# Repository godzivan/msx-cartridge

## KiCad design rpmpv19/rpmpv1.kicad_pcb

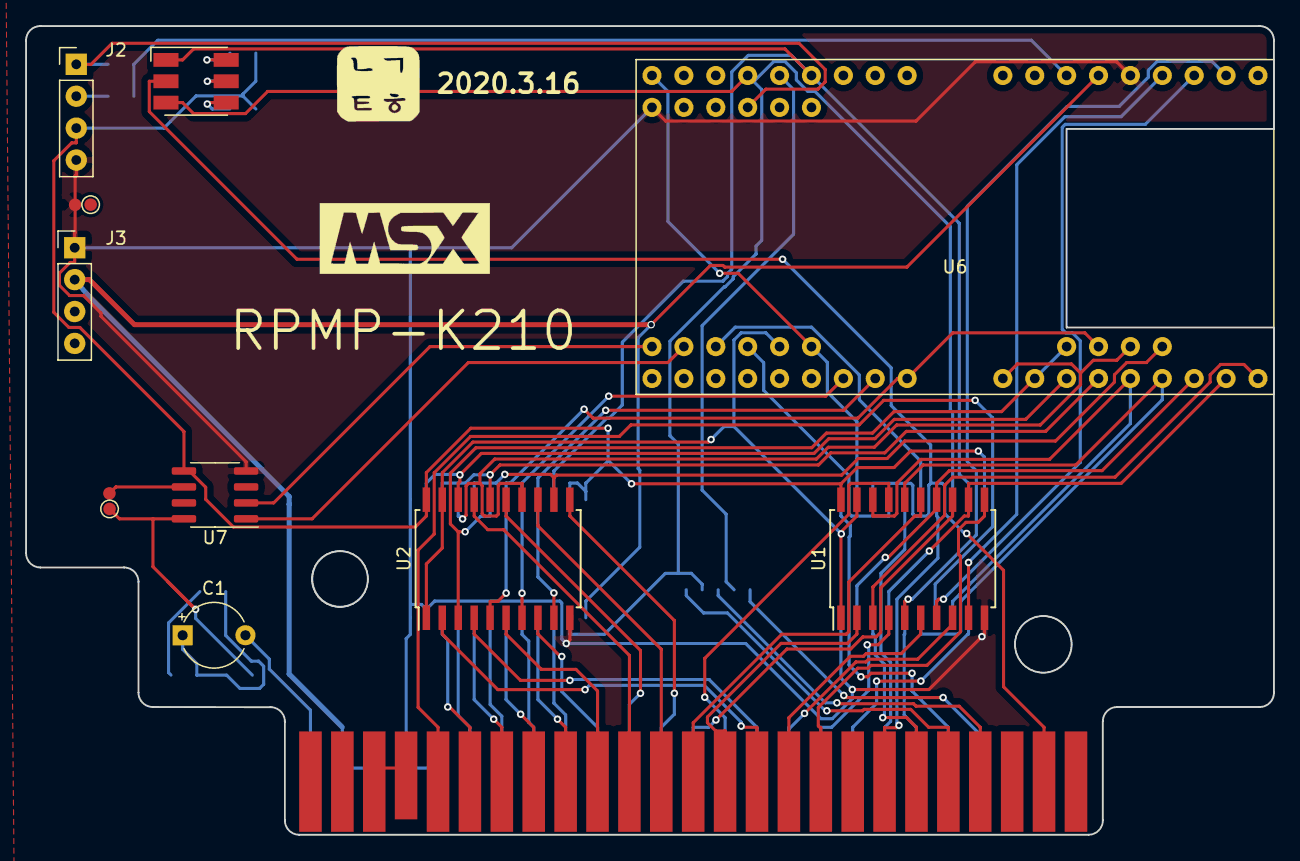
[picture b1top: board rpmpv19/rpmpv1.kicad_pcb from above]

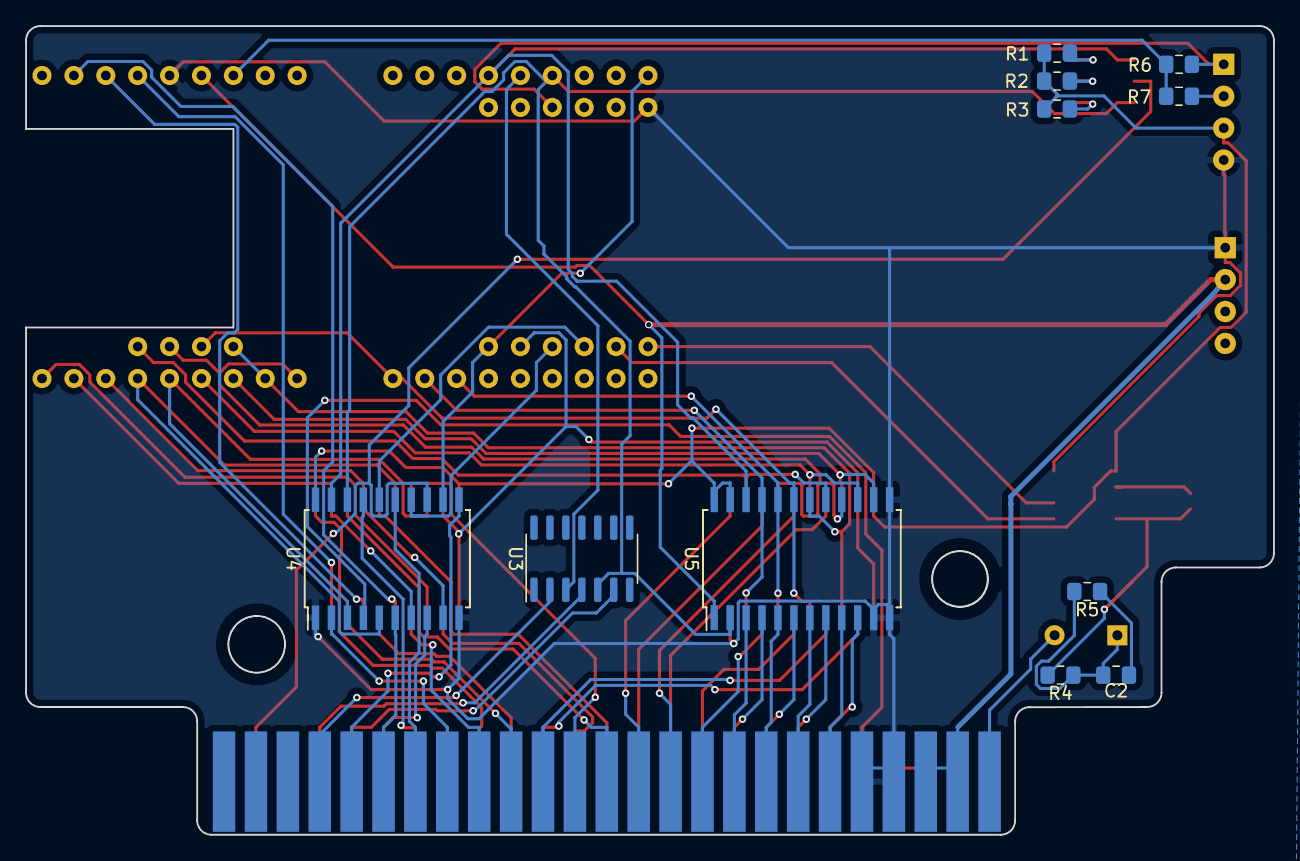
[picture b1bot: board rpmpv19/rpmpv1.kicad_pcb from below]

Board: 2 copper layers, 99.4 x 64.4 mm, 24 parts (11 on the bottom side), 75 nets.

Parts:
C1: CP; CP_Radial_Tantal_D5.0mm_P5.00mm
C2: C; C_0805_2012Metric_Pad1.15x1.40mm_HandSolder
D1: LED_RGB; LED_RGB_5050-6
G1: LOGO; srxg10
G2: LOGO
J2: Conn_01x04; PinHeader_1x04_P2.54mm_Vertical
J3: Conn_01x04_Male; PinHeader_1x04_P2.54mm_Vertical
P1: CONN_02X25; card_edge_connector
R1, R2, R3, R4, R5, R6, R7: R; R_0805_2012Metric_Pad1.15x1.40mm_HandSolder
U1, U2, U4: 74HC244; SOIC-20W_7.5x12.8mm_Pitch1.27mm
U3: 74LS07; SOIC-14_3.9x8.7mm_P1.27mm
U5: LVC4245; SOIC-24W_7.5x15.4mm_Pitch1.27mm
U6: SipeedMaixBit; maix_bit
U7: PT8211; SOIC-8_3.9x4.9mm_P1.27mm
W1, W2: TEST; TestPoint_Pad_D1.0mm

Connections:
/3V3: R6.1, R7.1, U6.49
/5V0: J3.2, P1.45, P1.47, U5.1, U6.48
/A0: P1.28, U2.13
/A1: P1.27, U2.11
/A2: P1.30, U2.17
/A3: P1.29, U2.15
/A4: P1.32, U2.6
/A5: P1.31, U2.8
/A6: P1.22, U2.2
/A7: P1.21, U2.4
/A8: P1.24, U1.2
/A9: P1.17, U1.4
/A10: P1.20, U1.6
/A11: P1.19, U1.8
/A12: P1.23, U1.17
/A13: P1.26, U1.15
/A14: P1.25, U1.13
/A15: P1.18, U1.11
/ADDR: U1.1, U1.19, U2.1, U2.19, U6.37
/BUSDIR: P1.10, U3.6
/CLK: P1.42, U4.4
/D0: P1.34, U5.4
/D1: P1.33, U5.3
/D2: P1.36, U5.6
/D3: P1.35, U5.5
/D4: P1.38, U5.8
/D5: P1.37, U5.7
/D6: P1.40, U5.10
/D7: P1.39, U5.9
/DAT_DIR: D1.3, U3.5, U4.18, U5.2, U6.32
/DAT_EN: D1.1, U4.19, U5.22, U6.30
/GND: J2.4, J3.1, P1.41, P1.43, U1.10, U2.10, U4.1, U4.10, U5.11, U5.12, U5.13, U6.47, U7.4, W2.2
/INT: P1.8, U3.4
/IORQ: P1.11, U4.6
/M1: P1.9, U4.11
/MREQ: P1.12, U4.8
/PCM_RCK: U6.40, U7.1
/PCM_WS: U6.41, U7.2
/RA8: U1.18, U4.3, U6.17
/RA9: U1.16, U4.5, U6.18
/RA10: U1.14, U4.9, U6.19
/RA11: U1.12, U4.7, U6.20
/RA12: U1.3, U6.21
/RA13: U1.5, U6.23
/RA14: U1.7, U6.24
/RA15: U1.9, U6.25
/RC17: U3.3, U6.31
/RC21: U4.12, U6.35, U6.36
/RC23: U4.14, U6.38
/RC24: U4.16, U6.39
/RD: P1.14, U4.17
/RD0: U2.7, U5.20, U6.6
/RD1: U2.9, U5.21, U6.7
/RD2: U2.3, U5.18, U6.10, U6.11
/RD3: U2.5, U5.19, U6.8, U6.12
/RD4: U2.14, U5.16, U6.9, U6.13
/RD5: U2.12, U5.17, U6.14
/RD6: U2.18, U5.14, U6.15
/RD7: U2.16, U5.15, U6.16
/RESET: P1.15, U4.2
/SCK: J2.2, R7.2
/SDA: J2.1, R6.2, U6.44
/SLTSL: D1.2, P1.4, U4.13
/SND: R4.2, U7.8, W1.1
/SND0: U7.6, W1.2
/SOUNDIN: C1.2, P1.49
/VCC: J2.3, R1.2, R2.2, R3.2, U1.20, U2.20, U4.20, U5.23, U5.24, U7.5
/WAIT: P1.7, U3.2
/WR: P1.13, U4.15
unnamed: C1.1, C2.2, R4.1, R5.2
unnamed: C2.1, R5.1
unnamed: D1.4, R3.1
unnamed: D1.5, R2.1
unnamed: D1.6, R1.1
unnamed: P1.44, P1.46

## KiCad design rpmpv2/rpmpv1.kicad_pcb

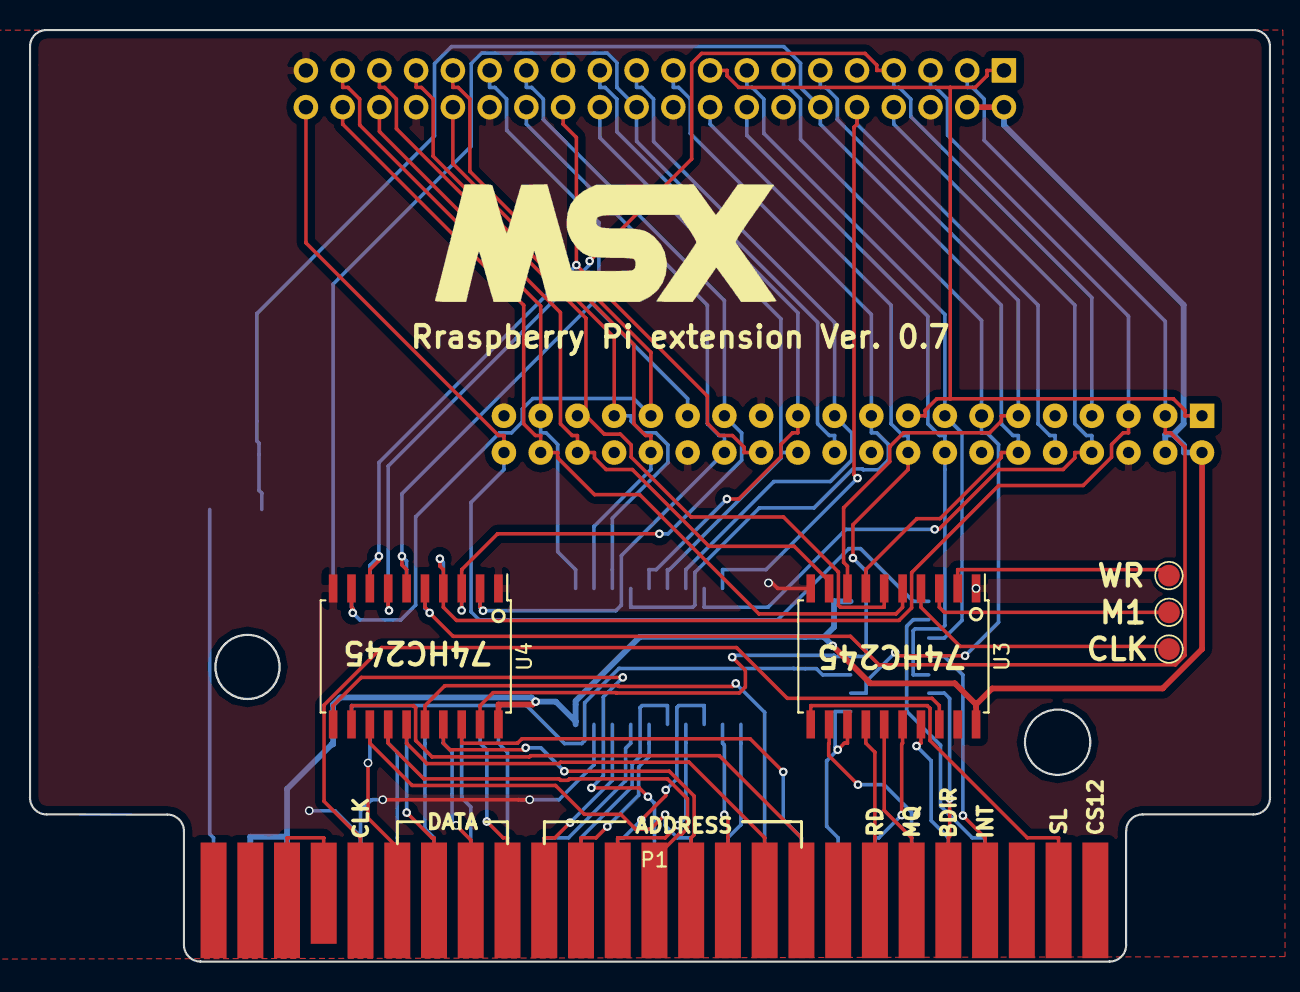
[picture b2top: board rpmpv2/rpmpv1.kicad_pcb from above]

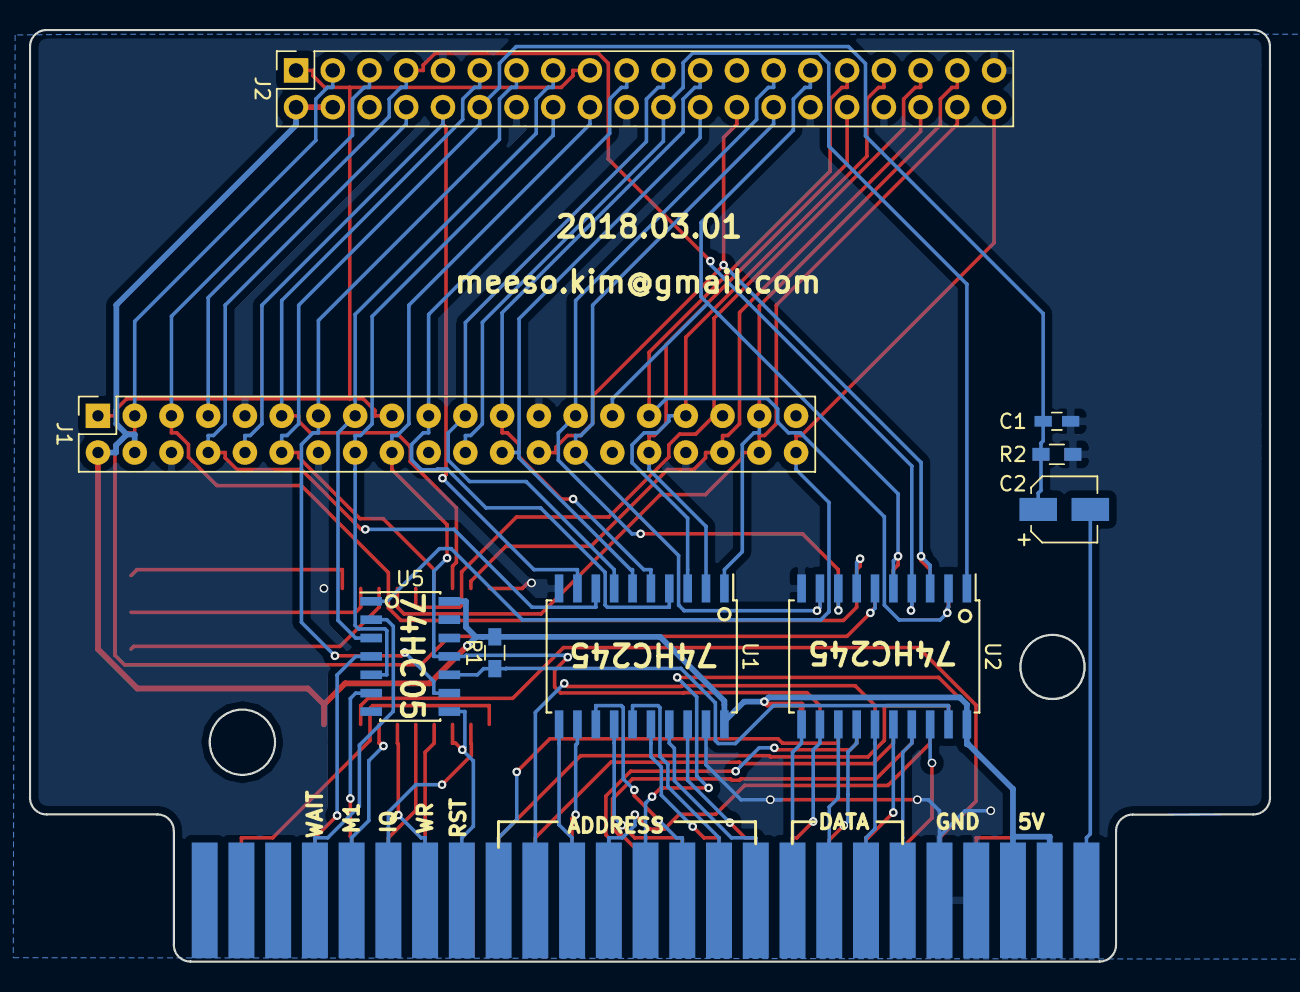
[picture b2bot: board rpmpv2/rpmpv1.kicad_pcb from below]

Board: 2 copper layers, 85.7 x 64.4 mm, 15 parts (9 on the bottom side), 72 nets.

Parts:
C1: C; C_0603_HandSoldering
C2: CP; CP_Elec_4x5.3
J1, J2: RPi_GPIO; Socket_Strip_Straight_2x20_Pitch2.54mm
J3, J4, J5: TEST_1P; TestPoint_Pad_D1.5mm
P1: CONN_02X25; card_edge_connector
R1, R2: R; R_0603_HandSoldering
U1, U2, U3, U4: 74LS245; SOIC-20W_7.5x12.8mm_Pitch1.27mm
U5: 74LS05; SOIC-14_3.9x8.7mm_Pitch1.27mm

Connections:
+3V3: J1.1, J1.17, J2.1, J2.17
+5V: J1.2, J1.4, J2.2, J2.4, P1.45, P1.47, R1.2, U1.20, U2.20, U3.20, U4.20, U5.14
/A0: P1.28, U1.14
/A1: P1.27, U1.13
/A2: P1.30, U1.16
/A3: P1.29, U1.15
/A4: P1.32, U1.18
/A5: P1.31, U1.17
/A6: P1.22, U1.12
/A7: P1.21, U1.11
/A8: P1.24, U4.17
/A9: P1.17, U4.18
/A10: P1.20, U4.15
/A11: P1.19, U4.16
/A12: P1.23, U4.13
/A13: P1.26, U4.14
/A14: P1.25, U4.11
/A15: P1.18, U4.12
/BUSDIR: P1.10, U5.6
/CLK: P1.42, U3.18
/D0: P1.34, U2.12
/D1: P1.33, U2.11
/D2: P1.36, U2.14
/D3: P1.35, U2.13
/D4: P1.38, U2.16
/D5: P1.37, U2.15
/D6: P1.40, U2.18
/D7: P1.39, U2.17
/INT: P1.8, U5.4
/IORQ: P1.11, U3.12
/M1: P1.9, U3.17
/MREQ: P1.12, U3.15
/RA8: J1.24, J2.24, U1.6
/RA9: J1.21, J2.21, U1.7
/RA10: J1.19, J2.19, U1.4
/RA11: J1.23, J2.23, U1.5
/RA12: J1.32, J2.32, U1.2
/RA13: J1.33, J2.33, U1.3
/RA14: J1.8, J2.8, U1.8
/RA15: J1.10, J2.10, U1.9
/RC16: J1.36, J2.36, U3.9
/RC17: J1.11, J2.11, U3.8
/RC18: C1.1, C2.1, J1.12, J2.12, R2.1, U3.7
/RC19: J1.35, J2.35, U3.6
/RC20: J1.38, J2.38, U3.5
/RC21: J1.40, J2.40, U5.1
/RC22: J1.15, J2.15, U5.3
/RC23: J1.16, J2.16, U5.5
/RC24: J1.18, J2.18, U4.19, U5.11
/RC25: J1.22, J2.22, U2.1
/RC26: J1.37, J2.37, U1.1
/RC27: J1.13, J2.13, U5.9
/RD: P1.14, U3.14
/RD0: J1.27, J2.27, U2.8, U4.3
/RD1: J1.28, J2.28, U2.9, U4.2
/RD2: J1.3, J2.3, U2.6, U4.5
/RD3: J1.5, J2.5, U2.7, U4.4
/RD4: J1.7, J2.7, U2.4, U4.7
/RD5: J1.29, J2.29, U2.5, U4.6
/RD6: J1.31, J2.31, U2.2, U4.9
/RD7: J1.26, J2.26, U2.3, U4.8
/RESET: P1.15, U3.13, U5.8
/SLTSL: P1.4, U3.11
/SOUNDIN: C2.2, P1.49
/TP0: J3.1, U3.4
/TP1: J4.1, U3.3
/TP2: J5.1, U3.2
/WAIT: P1.7, U5.2
/WR: P1.13, U3.16
/nRC24: R1.1, U2.19, U5.10
GND: C1.2, J1.6, J1.9, J1.14, J1.20, J1.25, J1.30, J1.34, J1.39, J2.6, J2.9, J2.14, J2.20, J2.25, J2.30, J2.34, J2.39, P1.41, P1.43, R2.2, U1.10, U1.19, U2.10, U3.1, U3.10, U3.19, U4.1, U4.10, U5.7
unnamed: P1.44, P1.46

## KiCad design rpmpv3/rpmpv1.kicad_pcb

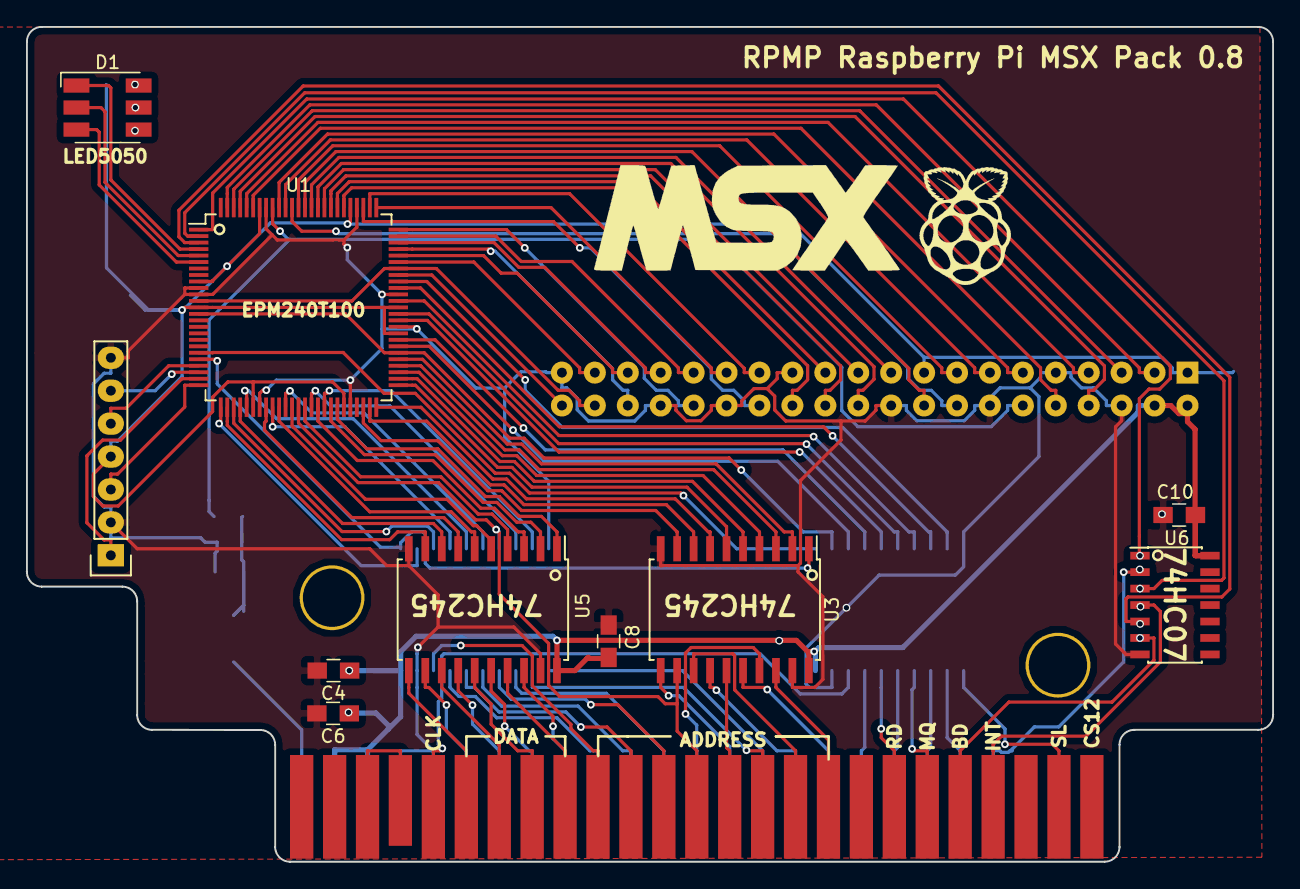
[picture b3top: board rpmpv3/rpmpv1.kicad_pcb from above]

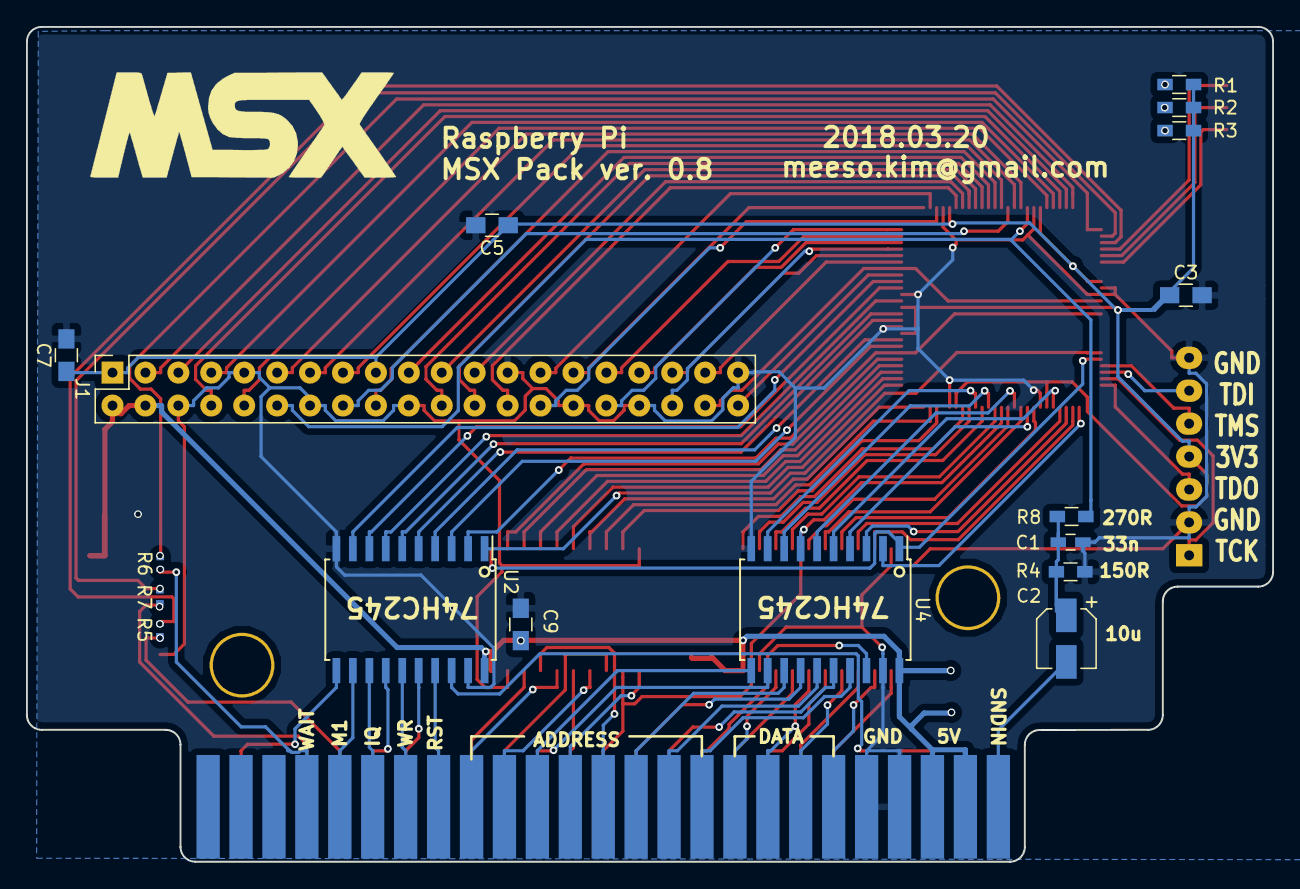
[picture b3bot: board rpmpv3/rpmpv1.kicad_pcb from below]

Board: 2 copper layers, 96.1 x 64.4 mm, 29 parts (18 on the bottom side), 116 nets.

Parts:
C1: C; C_0603_HandSoldering
C2: CP; CP_Elec_4x5.3
C3, C4, C5, C6, C7, C8, C9, C10: C; C_0805_HandSoldering
D1: LED_RGB; LED_RGB_5050-6
G2: LOGO; msx-logo
J1: RPi_GPIO; Socket_Strip_Straight_2x20_Pitch2.54mm
J2: Conn_01x07; Pin_Header_Straight_1x07
P1: CONN_02X25; card_edge_connector
R1, R2, R3, R4, R8: R; R_0603_HandSoldering
R5, R6, R7: R; R_0402_NoSilk
U1: MaxII_EPM240; TQFP-100_14x14mm_Pitch0.5mm
U2, U3, U4, U5: 74LS245; SOIC-20W_7.5x12.8mm_Pitch1.27mm
U6: 74LS05; SOIC-14_3.9x8.7mm_Pitch1.27mm

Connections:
+3V3: C3.1, C5.1, C7.1, J1.1, J1.17, J2.4, R1.1, R2.1, R3.1, U1.9, U1.13, U1.31, U1.45, U1.59, U1.63, U1.80, U1.94
+5V: C4.1, C6.1, C8.1, C9.1, C10.1, J1.2, J1.4, P1.45, P1.47, U2.20, U3.20, U4.20, U5.20, U6.14
/A0: P1.28, U4.14
/A1: P1.27, U4.13
/A2: P1.30, U4.16
/A3: P1.29, U4.15
/A03: U1.36, U4.6
/A4: P1.32, U4.18
/A5: P1.31, U4.17
/A6: P1.22, U4.12
/A7: P1.21, U4.11
/A8: P1.24, U3.15
/A9: P1.17, U3.16
/A10: P1.20, U3.13
/A11: P1.19, U3.14
/A12: P1.23, U3.11
/A13: P1.26, U1.38, U3.12, U4.7
/A14: P1.25, U3.17
/A15: P1.18, U3.18
/A23: U1.34, U4.4
/A33: U1.30, U4.5
/A43: U1.26, U4.2
/A53: U1.28, U4.3
/A63: U1.40, U4.8
/A73: U1.42, U4.9
/A83: U1.52, U3.5
/A93: U1.53, U3.4
/A103: U1.50, U3.7
/A113: U1.51, U3.6
/A123: U1.48, U3.9
/A133: U1.49, U3.8
/A143: U1.54, U3.3
/A153: U1.55, U3.2
/AD: U1.21, U3.1, U4.1
/BUSDIR: P1.10, R5.1, U6.6
/BUSDIR3: R5.2, U1.3, U6.5
/CD: U1.20, U2.1
/CLK: P1.42, U2.18
/CLK3: U1.14, U1.56, U2.2
/D0: P1.34, U5.17
/D1: P1.33, U5.18
/D2: P1.36, U5.15
/D3: P1.35, U5.16
/D03: U1.41, U5.3
/D4: P1.38, U5.13
/D5: P1.37, U5.14
/D6: P1.40, U5.11
/D7: P1.39, U5.12
/D13: U1.43, U5.2
/D23: U1.37, U5.5
/D33: U1.39, U5.4
/D43: U1.33, U5.7
/D53: U1.35, U5.6
/D63: U1.27, U5.9
/D73: U1.29, U5.8
/DD: U1.44, U5.1
/INT: P1.8, R7.1, U6.4
/INT3: R7.2, U1.2, U6.3
/IORQ: P1.11, U2.13
/IORQ3: U1.64, U2.7
/LED1: D1.1, U1.4
/LED2: D1.2, U1.5
/LED3: D1.3, U1.6
/M1: P1.9, U2.12
/M13: U1.66, U2.8
/MREQ: P1.12, U2.14
/MREQ3: U1.62, U2.6
/RA8: J1.24, U1.83
/RA9: J1.21, U1.84
/RA10: J1.19, U1.86
/RA11: J1.23, U1.82
/RA12: J1.32, U1.75
/RA13: J1.33, U1.73
/RA14: J1.8, U1.97
/RA15: J1.10, U1.95
/RC16: J1.36, U1.72
/RC17: J1.11, U1.91
/RC18: J1.12, R8.2, U1.92
/RC19: J1.35, U1.71
/RC20: J1.38, U1.12, U1.69
/RC21: J1.40, U1.68
/RC22: J1.15, U1.88
/RC23: J1.16, U1.89
/RC24: J1.18, U1.87
/RC25: J1.22, U1.85
/RC26: J1.37, U1.70
/RC27: J1.13, U1.90
/RD: P1.14, U2.16
/RD0: J1.27, U1.77
/RD1: J1.28, U1.78
/RD2: J1.3, U1.99
/RD3: J1.5, U1.98
/RD4: J1.7, U1.96
/RD5: J1.29, U1.76
/RD6: J1.31, U1.74
/RD7: J1.26, U1.81
/RD_3: U1.58, U2.4
/RESET: P1.15, U2.17
/RESET3: U1.57, U2.3
/SLTSL: P1.4, U2.11
/SLTSL3: U1.67, U2.9
/SOUNDIN: C2.2, P1.49
/TCK: J2.1, U1.24
/TDI: J2.6, U1.23
/TDO: J2.3, U1.25
/TMS: J2.5, U1.22
/WAIT: P1.7, R6.1, U6.2
/WAIT3: R6.2, U1.1, U6.1
/WR: P1.13, U2.15
/WR3: U1.61, U2.5
GND: C1.2, C3.2, C4.2, C5.2, C6.2, C7.2, C8.2, C9.2, C10.2, J1.6, J1.9, J1.14, J1.20, J1.25, J1.30, J1.34, J1.39, J2.2, J2.7, P1.41, P1.43, R4.2, U1.10, U1.11, U1.32, U1.46, U1.60, U1.65, U1.79, U1.93, U2.10, U2.19, U3.10, U3.19, U4.10, U4.19, U5.10, U5.19, U6.7
unnamed: C1.1, C2.1, R4.1, R8.1
unnamed: D1.4, R3.2
unnamed: D1.5, R2.2
unnamed: D1.6, R1.2
unnamed: P1.44, P1.46

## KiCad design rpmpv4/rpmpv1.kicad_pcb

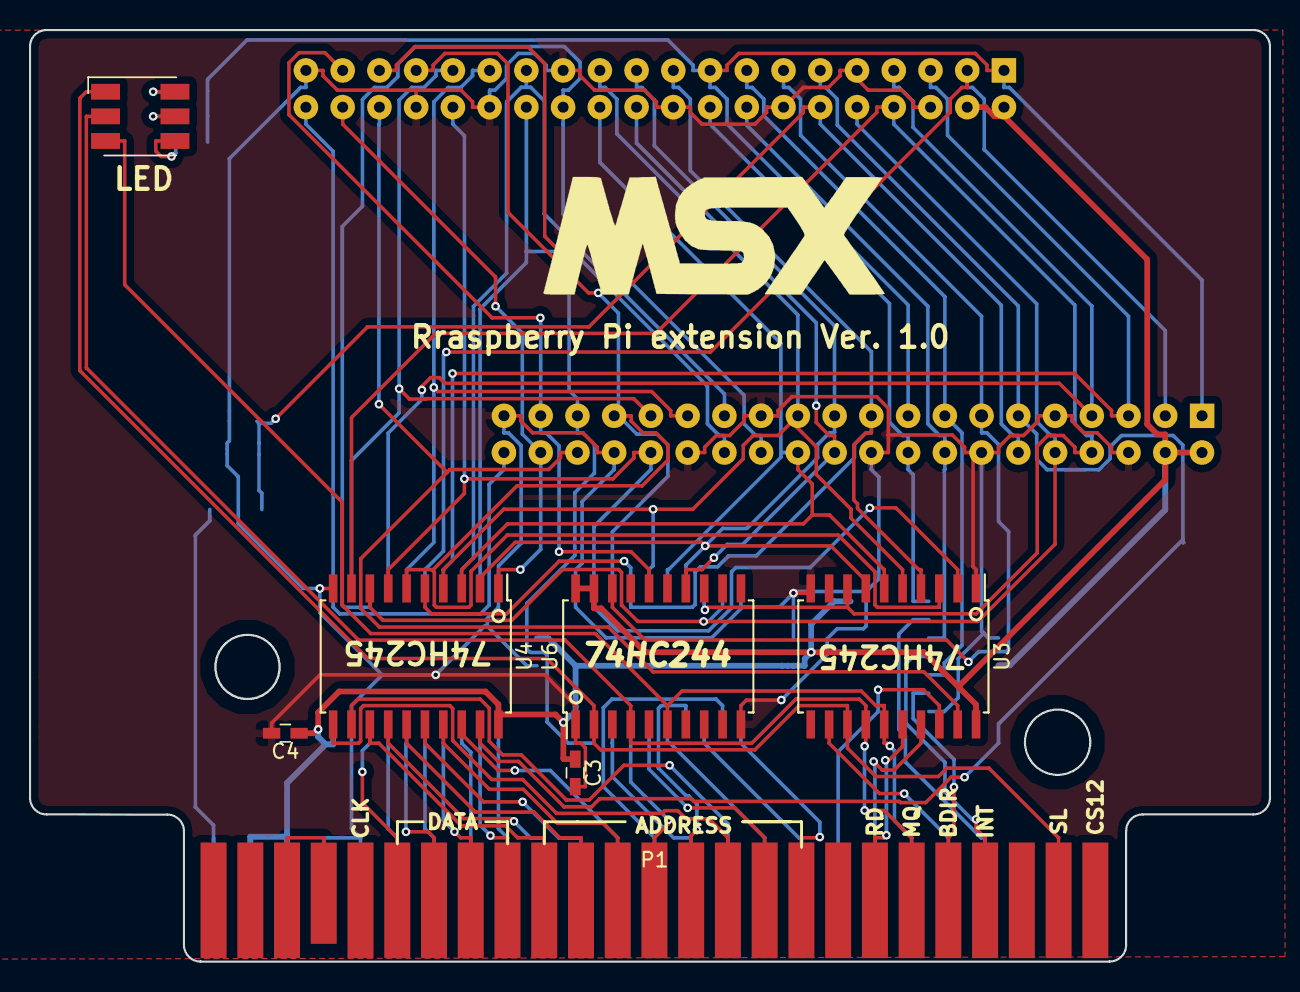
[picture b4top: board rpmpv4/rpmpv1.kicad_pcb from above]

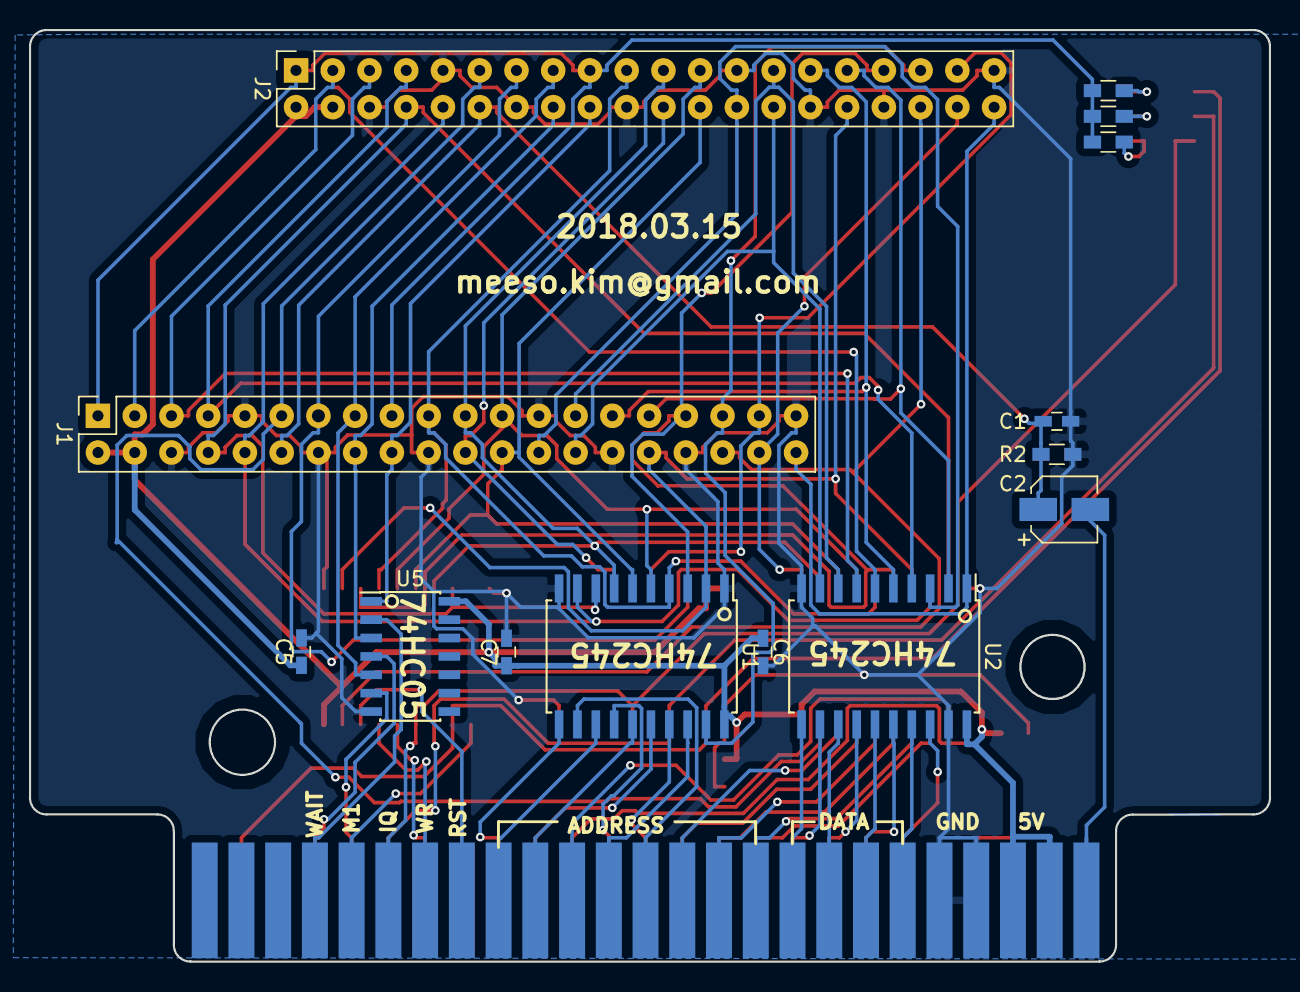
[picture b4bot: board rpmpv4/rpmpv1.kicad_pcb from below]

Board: 2 copper layers, 85.7 x 64.4 mm, 21 parts (14 on the bottom side), 70 nets.

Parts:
C1, C3, C4, C5, C6, C7: C; C_0603_HandSoldering
C2: CP; CP_Elec_4x5.3
D1: LED_RGB; LED_RGB_5050-6
J1, J2: RPi_GPIO; Socket_Strip_Straight_2x20_Pitch2.54mm
P1: CONN_02X25; card_edge_connector
R1, R2, R3, R4: R; R_0603_HandSoldering
U1, U2, U3, U4: 74LS245; SOIC-20W_7.5x12.8mm_Pitch1.27mm
U5: 74LS05; SOIC-14_3.9x8.7mm_Pitch1.27mm
U6: 74HC244; SOIC-20W_7.5x12.8mm_Pitch1.27mm

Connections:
+3V3: J1.1, J1.17, J2.1, J2.17, R1.1, R3.1, R4.1
+5V: C3.1, C4.1, C5.1, C6.1, C7.1, J1.2, J1.4, J2.2, J2.4, P1.45, P1.47, U1.20, U2.20, U3.20, U4.20, U5.14, U6.19, U6.20
/A0: P1.28, U4.17
/A1: P1.27, U4.18
/A2: P1.30, U4.15
/A3: P1.29, U4.16
/A4: P1.32, U4.13
/A5: P1.31, U4.14
/A6: P1.22, U4.11
/A7: P1.21, U4.12
/A8: P1.24, U1.14
/A9: P1.17, U1.13
/A10: P1.20, U1.16
/A11: P1.19, U1.15
/A12: P1.23, U1.18
/A13: P1.26, U1.17
/A14: P1.25, U1.12
/A15: P1.18, U1.11
/BUSDIR: P1.10, U5.6
/D0: P1.34, U2.12
/D1: P1.33, U2.11
/D2: P1.36, U2.14
/D3: P1.35, U2.13
/D4: P1.38, U2.16
/D5: P1.37, U2.15
/D6: P1.40, U2.18
/D7: P1.39, U2.17
/INT: P1.8, U5.4
/IORQ: D1.3, P1.11, U3.15, U6.6
/M1: P1.9, U3.12
/MREQ: D1.2, P1.12, U3.14, U6.4
/RA8: J1.24, J2.24, U1.6, U3.6, U4.3
/RA9: J1.21, J2.21, U1.7, U3.7, U4.2
/RA10: J1.19, J2.19, U1.4, U3.4, U4.5
/RA11: J1.23, J2.23, U1.5, U3.5, U4.4
/RA12: J1.32, J2.32, U1.2, U3.2, U4.7
/RA13: J1.33, J2.33, U1.3, U3.3, U4.6
/RA14: J1.8, J2.8, U1.8, U3.8, U4.9
/RA15: J1.10, J2.10, U1.9, U4.8
/RC16: J1.36, J2.36, U3.19
/RC17: J1.11, J2.11, U4.19
/RC18: C1.1, C2.1, J1.12, J2.12, R2.1
/RC19: J1.35, J2.35, U1.19
/RC20: J1.38, J2.38, U4.1
/RC21: J1.40, J2.40, U2.1
/RC22: J1.15, J2.15, U5.5
/RC23: J1.16, J2.16, U5.3
/RC24: J1.18, J2.18, U5.1
/RC25: J1.22, J2.22, U6.14
/RC26: J1.37, J2.37, U6.16
/RC27: J1.13, J2.13, U6.18
/RD: P1.14, U3.16
/RD0: J1.27, J2.27, U2.8
/RD1: J1.28, J2.28, U2.9
/RD2: J1.3, J2.3, U2.6
/RD3: J1.5, J2.5, U2.7
/RD4: J1.7, J2.7, U2.4
/RD5: J1.29, J2.29, U2.5
/RD6: J1.31, J2.31, U2.2
/RD7: J1.26, J2.26, U2.3
/RESET: P1.15, U3.18
/SLTSL: D1.1, P1.4, U3.13, U6.2
/SOUNDIN: C2.2, P1.49
/WAIT: P1.7, U5.2
/WR: P1.13, U3.17
GND: C1.2, C3.2, C4.2, C5.2, C6.2, C7.2, J1.6, J1.9, J1.14, J1.20, J1.25, J1.30, J1.34, J1.39, J2.6, J2.9, J2.14, J2.20, J2.25, J2.30, J2.34, J2.39, P1.41, P1.43, R2.2, U1.1, U1.10, U2.10, U2.19, U3.1, U3.10, U4.10, U5.7, U6.1, U6.10
unnamed: D1.4, R4.2
unnamed: D1.5, R3.2
unnamed: D1.6, R1.2
unnamed: P1.44, P1.46

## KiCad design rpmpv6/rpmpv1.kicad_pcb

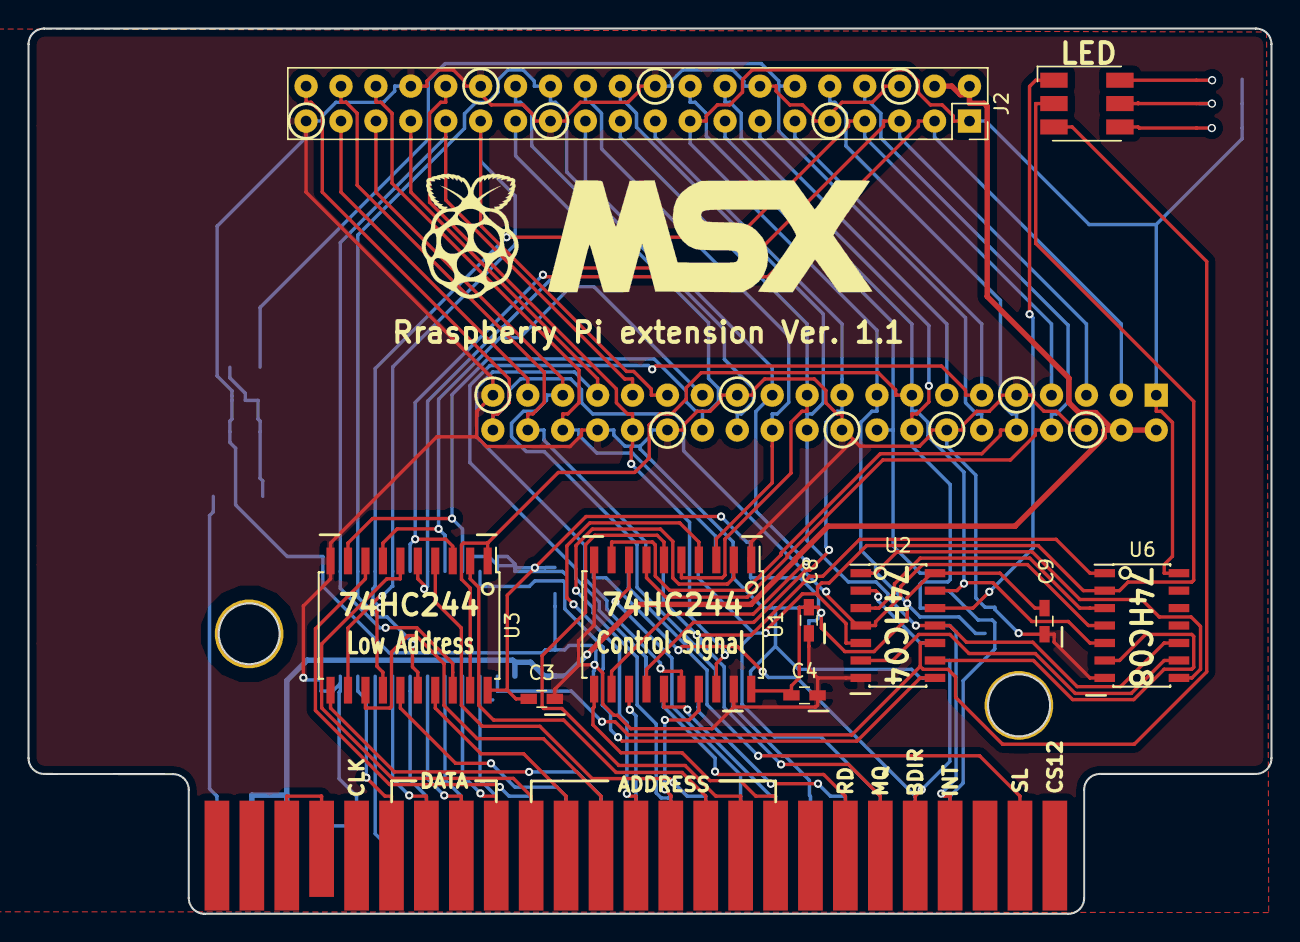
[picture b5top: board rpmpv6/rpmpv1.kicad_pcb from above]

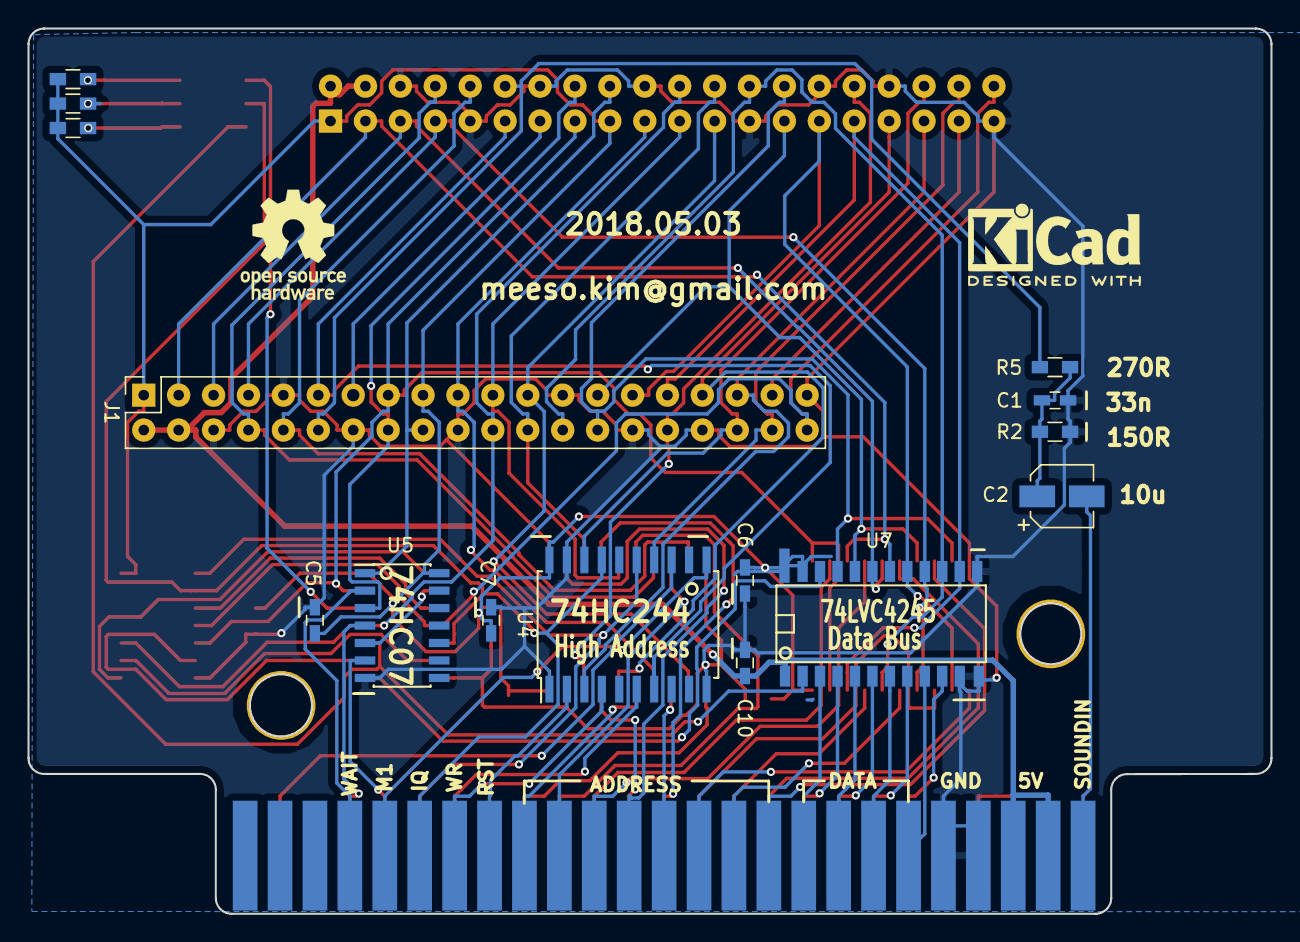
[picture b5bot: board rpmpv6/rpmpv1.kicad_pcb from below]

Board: 2 copper layers, 90.4 x 64.4 mm, 29 parts (17 on the bottom side), 79 nets.

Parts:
C1, C3, C4, C5, C6, C7, C8, C9, C10: C; C_0603_HandSoldering
C2: CP; CP_Elec_4x4.5
D1: LED_RGB; LED_RGB_5050-6
G1: LOGO; raspberry_pi_logo
J1, J2: RPi_GPIO; Socket_Strip_Straight_2x20_Pitch2.54mm
P1: CONN_02X25; card_edge_connector
R1, R2, R3, R4, R5: R; R_0603_HandSoldering
REF2: OSHW-Logo_7.5x8mm_SilkScreen
REF3: KiCad-Logo2_6mm_SilkScreen
U1, U3, U4: 74HC244; SOIC-20W_7.5x12.8mm_Pitch1.27mm
U2: 74HC04; SOIC-14_3.9x8.7mm_Pitch1.27mm
U5: 74LS07; SOIC-14_3.9x8.7mm_Pitch1.27mm
U6: 74LS08; SOIC-14_3.9x8.7mm_Pitch1.27mm
U7: LVC4245; SOIC-24@

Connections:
+3V3: C3.1, C4.1, C5.1, C6.1, C7.1, C8.1, C9.1, J1.1, J1.17, J2.1, J2.17, R1.1, R3.1, R4.1, U1.20, U2.14, U3.20, U4.20, U5.14, U6.14, U7.23, U7.24
+5V: C10.2, J1.2, J1.4, J2.2, J2.4, P1.45, P1.47, U7.1
/A0: P1.28, U3.13
/A1: P1.27, U3.11
/A2: P1.30, U3.17
/A3: P1.29, U3.15
/A4: P1.32, U3.6
/A5: P1.31, U3.8
/A6: P1.22, U3.2
/A7: P1.21, U3.4
/A8: P1.24, U1.17
/A9: P1.17, U1.15
/A10: P1.20, U1.6
/A11: P1.19, U1.8
/A12: P1.23, U1.2
/A13: P1.26, U1.4
/A14: P1.25, U1.13
/A15: P1.18, U1.11
/ATN: J1.40, J2.40, U2.4, U6.4
/BDIR: U2.2, U5.5
/BUSDIR: P1.10, U5.6
/D0: P1.34, U7.4
/D1: P1.33, U7.3
/D2: P1.36, U7.6
/D3: P1.35, U7.5
/D4: P1.38, U7.8
/D5: P1.37, U7.7
/D6: P1.40, U7.10
/D7: P1.39, U7.9
/DAT_DIR: D1.3, U2.10, U7.2
/DAT_EN: U2.8, U7.22
/INT: P1.8, U5.4
/IORQ: D1.2, P1.11, U2.5, U4.17, U6.2
/M1: P1.9, U4.11
/MREQ: P1.12, U4.15, U6.1
/RA8: J1.24, J2.24, U1.3
/RA9: J1.21, J2.21, U1.5
/RA10: J1.19, J2.19, U1.14
/RA11: J1.23, J2.23, U1.12
/RA12: J1.32, J2.32, U1.18
/RA13: J1.33, J2.33, U1.16
/RA14: J1.8, J2.8, U1.7
/RA15: J1.10, J2.10, U1.9
/RATN: J1.15, J2.15, U2.13, U3.1, U3.19, U6.5
/RC16: J1.36, J2.36, U4.18
/RC17: J1.11, J2.11, U4.7
/RC18: J1.12, J2.12, R5.1
/RC19: J1.35, J2.35, U4.3
/RC20: J1.38, J2.38, U4.14
/RC23: J1.16, J2.16, U5.3
/RC24: J1.18, J2.18, U5.1
/RC25: J1.22, J2.22, U2.11, U6.10
/RC26: J1.37, J2.37
/RC27: J1.13, J2.13
/RD: P1.14, U4.6
/RD0: J1.27, J2.27, U3.7, U7.20
/RD1: J1.28, J2.28, U3.9, U7.21
/RD2: J1.3, J2.3, U3.3, U7.18
/RD3: J1.5, J2.5, U3.5, U7.19
/RD4: J1.7, J2.7, U3.14, U7.16
/RD5: J1.29, J2.29, U3.12, U7.17
/RD6: J1.31, J2.31, U3.18, U7.14
/RD7: J1.26, J2.26, U3.16, U7.15
/RESET: P1.15, U4.2
/SLTSL: P1.4, U4.13
/SOUNDIN: C2.2, P1.49
/WAIT: P1.7, U5.2
/WR: P1.13, U4.4
/nATN: U2.3, U6.3
/nBDIR: U2.1, U6.8
/nDAT_EN: U2.9, U6.6
/nIORQ: U2.6, U6.9
/nRATN: D1.1, U2.12
GND: C1.2, C3.2, C4.2, C5.2, C6.2, C7.2, C8.2, C9.2, C10.1, J1.6, J1.9, J1.14, J1.20, J1.25, J1.30, J1.34, J1.39, J2.6, J2.9, J2.14, J2.20, J2.25, J2.30, J2.34, J2.39, P1.41, P1.43, R2.2, U1.1, U1.10, U1.19, U2.7, U3.10, U4.1, U4.10, U4.19, U5.7, U6.7, U7.11, U7.12, U7.13
unnamed: C1.1, C2.1, R2.1, R5.2
unnamed: D1.4, R4.2
unnamed: D1.5, R3.2
unnamed: D1.6, R1.2
unnamed: P1.44, P1.46
